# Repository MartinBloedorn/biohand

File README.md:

# biohand
Files and documentation for the Biohand project. 

You can follow the development of the prototype in [my personal page](http://martinvb.com) or in  [Hackday](https://hackaday.io/project/6411-biohand-low-cost-3d-printed-hand-prosthesis).

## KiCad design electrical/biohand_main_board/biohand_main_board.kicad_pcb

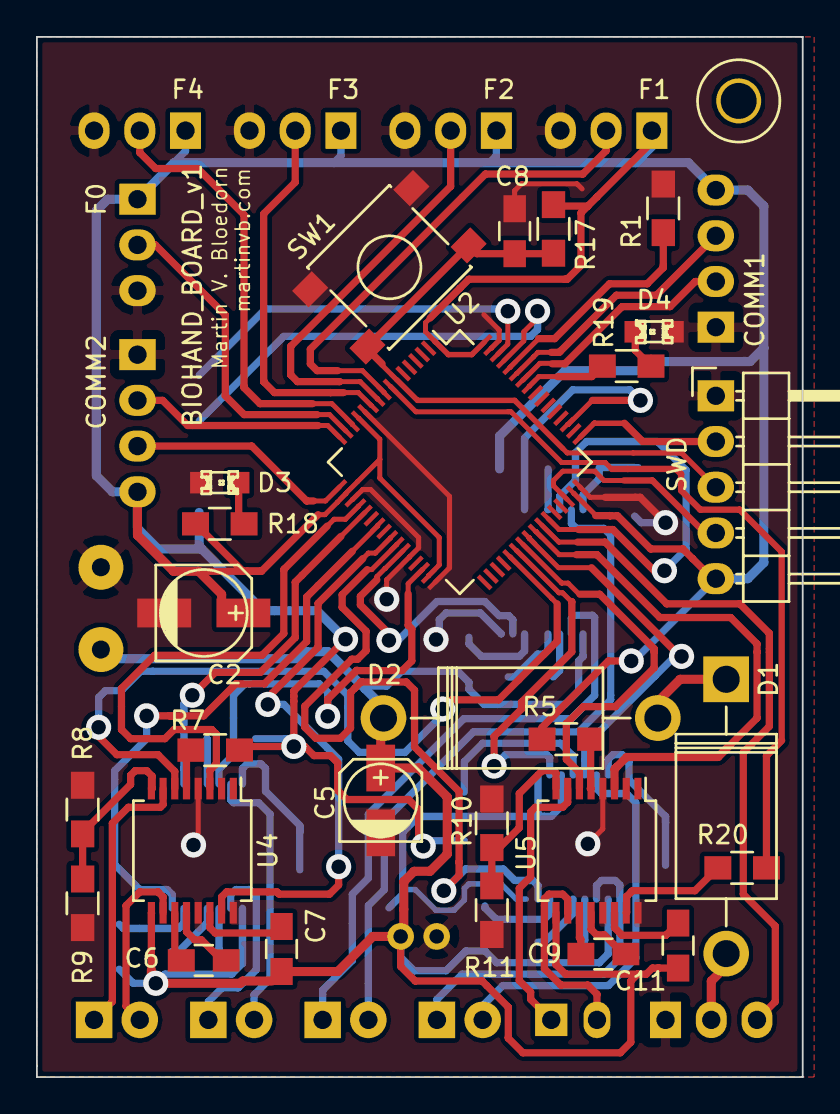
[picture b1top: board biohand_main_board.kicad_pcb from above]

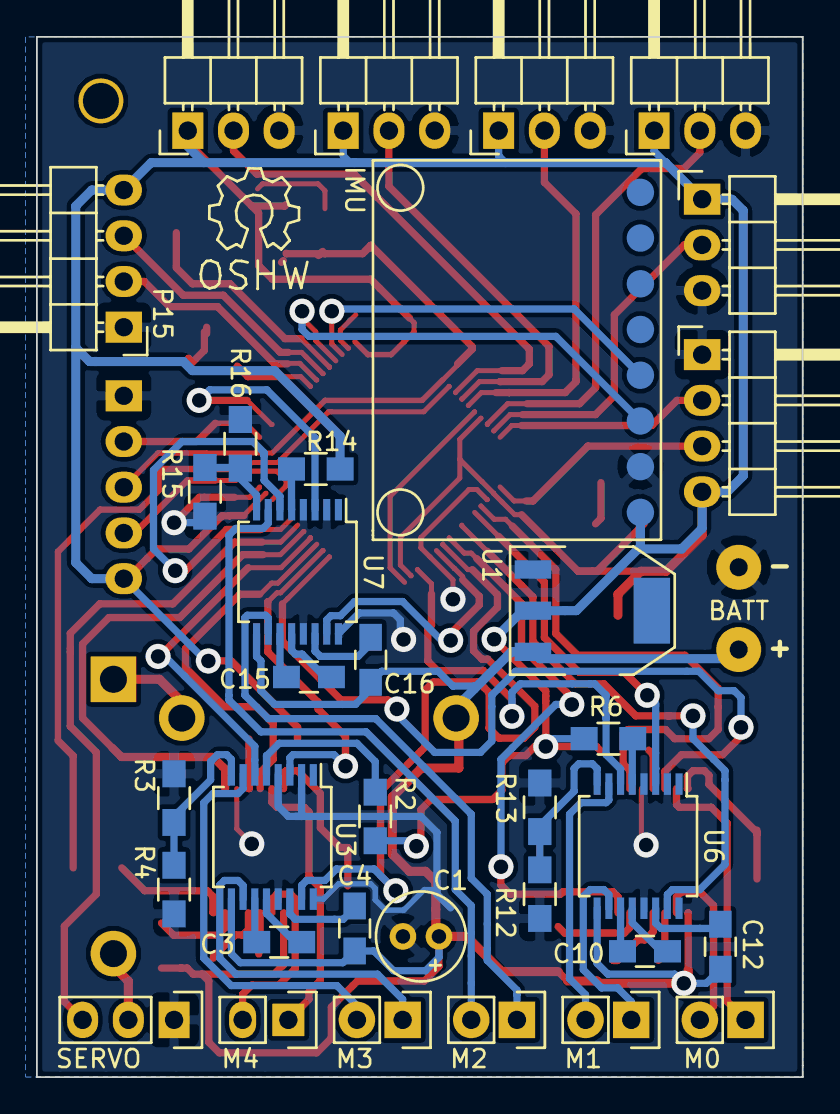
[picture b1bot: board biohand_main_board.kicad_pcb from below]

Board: 2 copper layers, 42.5 x 57.8 mm, 62 parts (35 on the bottom side), 75 nets.

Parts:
BATT: CONN_BATT; WireConnection_1mmDrill
C1: 10uF; Elko_vert_11x5mm_RM2
C2: 10uF; c_elec_5x5.3
C3, C6, C8, C9, C10, C15: C; C_0805_HandSoldering
C4, C7, C11, C12, C16: 0.1uF; C_0805_HandSoldering
C5: 10uF; c_elec_4x5.3
D1, D2: D; Diode_DO-201AD_Horizontal_RM15
D3, D4: LED; LED-0805
IMU: MPU6050-BrOut
P2: CONN_DRV3; Pin_Header_Straight_1x02
P3: CONN_DRV0; Pin_Header_Straight_1x02
P4: CONN_DRV1; Pin_Header_Straight_1x02
P5: CONN_DRV4; Pin_Header_Straight_1x02
P6: CONN_DRV2; Pin_Header_Straight_1x02
P7: CONN_POT0; Pin_Header_Angled_1x03
P8: CONN_POT1; Pin_Header_Angled_1x03
P9: CONN_POT2; Pin_Header_Angled_1x03
P10: CONN_POT3; Pin_Header_Angled_1x03
P11: CONN_POT4; Pin_Header_Angled_1x03
P12: CONN_SERVO; Pin_Header_Straight_1x03
P14: CONN_UART2; Pin_Header_Angled_1x04
P15: CONN_UART1; Pin_Header_Angled_1x04
R1: 100k; R_0805_HandSoldering
R2, R5, R6, R7, R14: 1k; R_0805_HandSoldering
R3, R4, R8, R9, R10, R11, R12, R13, R15, R16: R; R_0805_HandSoldering
R17: 10k; R_0805_HandSoldering
R18, R19: 470r; R_0805_HandSoldering
R20: 0r; R_0805_HandSoldering
SW1: SW_PUSH; SW_SPST_PTS645
SWD: CONN_SWD; Pin_Header_Angled_1x05
U1: LD1117S33TR; SOT-223
U2: STM32F103; LQFP-64_10x10mm_Pitch0.5mm
U3, U4, U5, U6, U7: DRV8801; SSOP-16_5.3x6.2mm_Pitch0.65mm

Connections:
+3V3: C2.1, IMU.1, P7.1, P8.1, P9.1, P10.1, P11.1, P14.4, P15.4, R2.2, R5.2, R6.2, R7.2, R14.2, R17.2, R18.2, SWD.5, U1.2, U2.1, U2.13, U2.18, U2.31, U2.47, U2.64
+BATT: BATT.2, C1.1, C4.1, C5.1, C7.1, C11.1, C12.1, C16.1, D2.1, U1.3, U3.9, U4.9, U5.9, U6.9, U7.9
/ADC_IN10: R20.1, U2.8
/NRST: C8.1, R17.1, SW1.2, SWD.3, U2.7
/POT0: P7.2, U2.15
/POT1: P8.2, U2.9
/POT2: P9.2, U2.10
/POT3: P10.2, U2.11
/POT4: P11.2, U2.14
/RX1: P15.3, U2.59
/RX2: P14.3, U2.17
/SCL: IMU.3, U2.61
/SDA: IMU.4, U2.62
/SERVO_SIG: P12.3, U2.42
/SWCLK: SWD.2, U2.49
/SWDIO: SWD.4, U2.46
/TX1: P15.2, U2.58
/TX2: P14.2, U2.16
GND: BATT.1, C1.2, C2.2, C5.2, C8.2, D3.2, D4.2, IMU.2, P7.3, P8.3, P9.3, P10.3, P11.3, P12.1, P14.1, P15.1, R1.1, R3.1, R4.1, R8.1, R9.1, R10.1, R11.1, R12.1, R13.1, R15.1, R16.1, SW1.1, SWD.1, U1.1, U2.12, U2.19, U2.28, U2.32, U2.48, U2.63, U3.2, U3.4, U3.13, U3.16, U4.2, U4.4, U4.13, U4.16, U5.2, U5.4, U5.13, U5.16, U6.2, U6.4, U6.13, U6.16, U7.2, U7.4, U7.13, U7.16
unnamed: C3.1, U3.11
unnamed: C3.2, U3.12
unnamed: C4.2, U3.14
unnamed: C6.1, U4.11
unnamed: C6.2, U4.12
unnamed: C7.2, U4.14
unnamed: C9.1, U5.11
unnamed: C9.2, U5.12
unnamed: C10.1, U6.11
unnamed: C10.2, U6.12
unnamed: C11.2, U5.14
unnamed: C12.2, U6.14
unnamed: C15.1, U7.11
unnamed: C15.2, U7.12
unnamed: C16.2, U7.14
unnamed: D1.1, D2.2
unnamed: D1.2, P12.2
unnamed: D3.1, R18.1
unnamed: D4.1, R19.1
unnamed: P2.1, U3.10
unnamed: P2.2, U3.7
unnamed: P3.1, U4.7
unnamed: P3.2, U4.10
unnamed: P4.1, U5.7
unnamed: P4.2, U5.10
unnamed: P5.1, U6.10
unnamed: P5.2, U6.7
unnamed: P6.1, U7.10
unnamed: P6.2, U7.7
unnamed: R1.2, U2.60
unnamed: R2.1, U3.5
unnamed: R3.2, R4.2, U3.8
unnamed: R5.1, U5.5
unnamed: R6.1, U6.5
unnamed: R7.1, U4.5
unnamed: R8.2, R9.2, U4.8
unnamed: R10.2, R11.2, U5.8
unnamed: R12.2, R13.2, U6.8
unnamed: R14.1, U7.5
unnamed: R15.2, R16.2, U7.8
unnamed: R19.2, U2.57
enable0: U2.37, U4.6
enable1: U2.39, U5.6
enable2: U2.43, U7.6
enable3: U2.40, U3.6
enable4: U2.30, U6.6
phase0: U2.20, U4.3
phase1: U2.41, U5.3
phase2: U2.51, U7.3
phase3: U2.38, U3.3
phase4: U2.21, U6.3
vpropi0: U2.25, U4.15
vpropi1: R20.2, U5.15
vpropi2: U2.27, U7.15
vpropi3: U2.26, U3.15
vpropi4: U2.23, U6.15

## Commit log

2018-03-12 Adding all files for first version.
